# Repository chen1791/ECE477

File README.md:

# ECE477
Files for ECE 477 Smart Cart senior design project for Team 4.

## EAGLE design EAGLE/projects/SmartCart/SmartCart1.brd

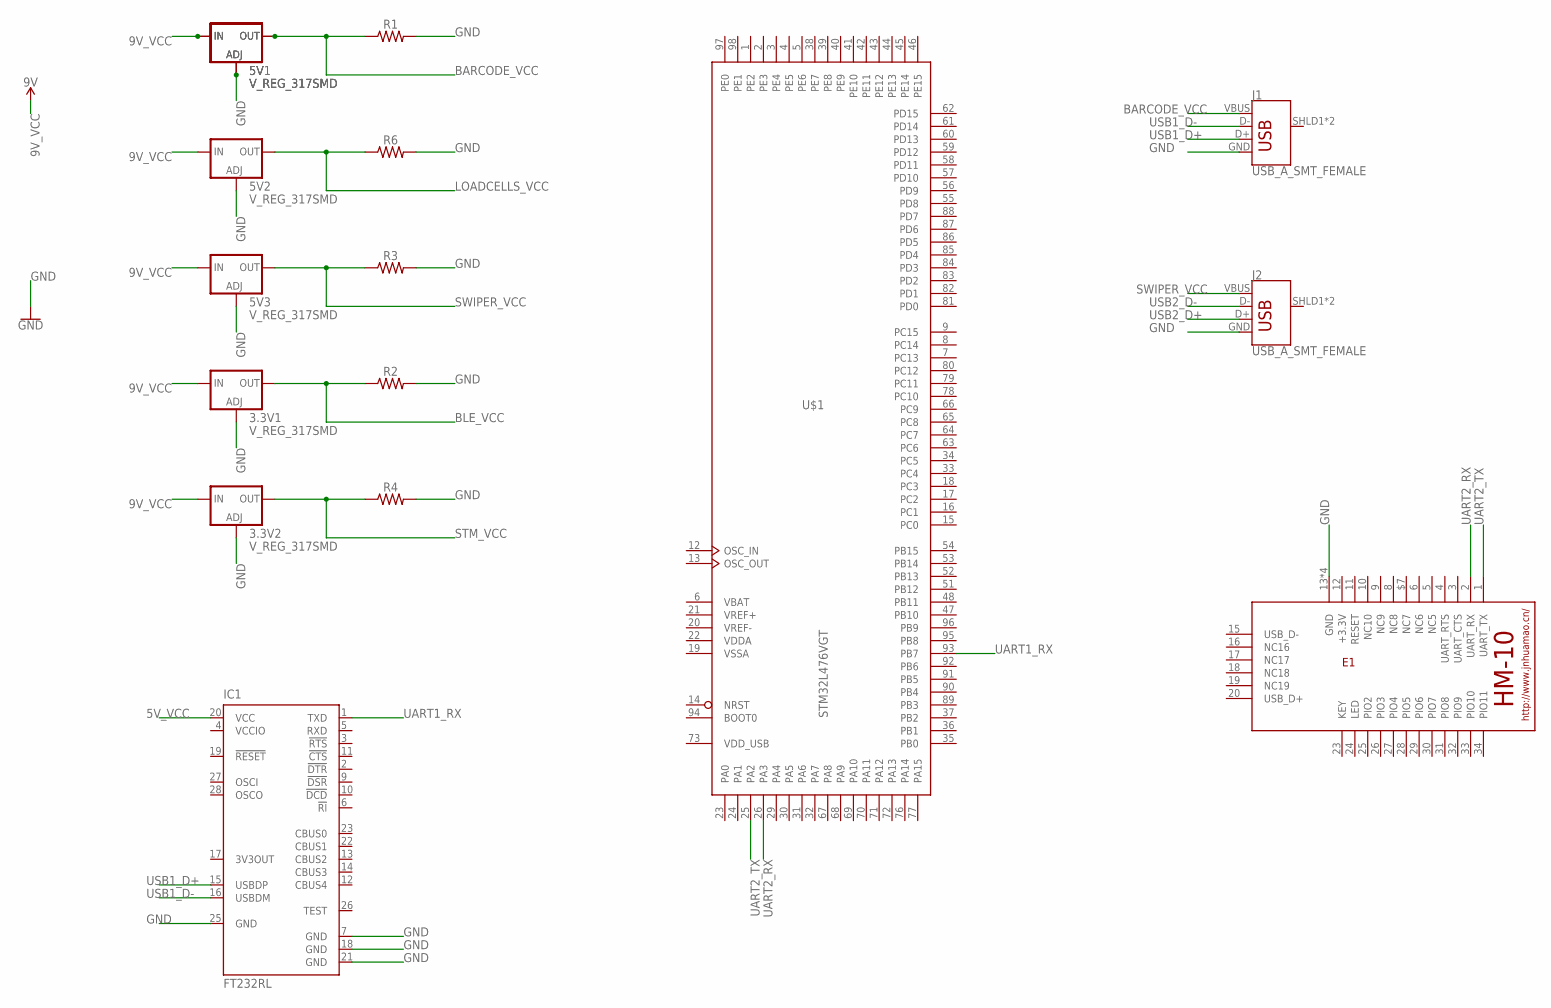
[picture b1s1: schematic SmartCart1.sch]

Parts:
3.3V1, 3.3V2, 5V, 5V1, 5V2, 5V3: V_REG_317SMD; SOT223
E1: HM-10-BOARD; 26.9X13X2.2_BOARD
IC1: FT232RL; SSOP28
J1, J2: USB_A_SMT_FEMALE; USB-A-S-SILK-FEMALE
R1, R2, R3, R4, R6: 0805
U$1: STM32L476VGT; LQFP100

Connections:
5V_VCC: IC1.20 (VCC)
9V_VCC: 3.3V1.3 (IN), 3.3V2.3 (IN), 5V.3 (IN), 5V1.3 (IN), 5V2.3 (IN), 5V3.3 (IN)
BARCODE_VCC: 5V.2 (OUT), 5V1.2 (OUT), J1.VBUS, R1.1
BLE_VCC: 3.3V1.2 (OUT), R2.1
GND: 3.3V1.1 (ADJ), 3.3V2.1 (ADJ), 5V.1 (ADJ), 5V1.1 (ADJ), 5V2.1 (ADJ), 5V3.1 (ADJ), E1.6 (NC6), E1.13 (GND), E1.14 (GND), E1.21 (GND), E1.22 (GND), IC1.7 (GND), IC1.18 (GND), IC1.21 (GND), IC1.25 (GND), J1.GND, J2.GND, R1.2, R2.2, R3.2, R4.2, R6.2
LOADCELLS_VCC: 5V2.2 (OUT), R6.1
STM_VCC: 3.3V2.2 (OUT), R4.1
SWIPER_VCC: 5V3.2 (OUT), E1.9 (NC9), J2.VBUS, R3.1
UART1_RX: IC1.1 (TXD), U$1.93 (PB7)
UART2_RX: E1.2 (UART_RX), U$1.26 (PA3)
UART2_TX: E1.1 (UART_TX), U$1.25 (PA2)
USB1_D+: IC1.15 (USBDP), J1.D+
USB1_D-: IC1.16 (USBDM), J1.D-
USB2_D+: E1.$7 (NC7), J2.D+
USB2_D-: E1.8 (NC8), J2.D-
VBAT: U$1.6 (VBAT)
VCCIO: IC1.4 (VCCIO)
VDD: U$1.11 (VDD), U$1.28 (VDD), U$1.50 (VDD), U$1.75 (VDD), U$1.100 (VDD)
VDDA: U$1.22 (VDDA)
VDD_USB: U$1.73 (VDD_USB)
VREF+: U$1.21 (VREF+)
VREF-: U$1.20 (VREF-)
VSS: U$1.10 (VSS), U$1.27 (VSS), U$1.49 (VSS), U$1.74 (VSS), U$1.99 (VSS)
VSSA: U$1.19 (VSSA)

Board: 2 copper layers, 16 parts (0 on the bottom side), 16 nets, no tracks yet.

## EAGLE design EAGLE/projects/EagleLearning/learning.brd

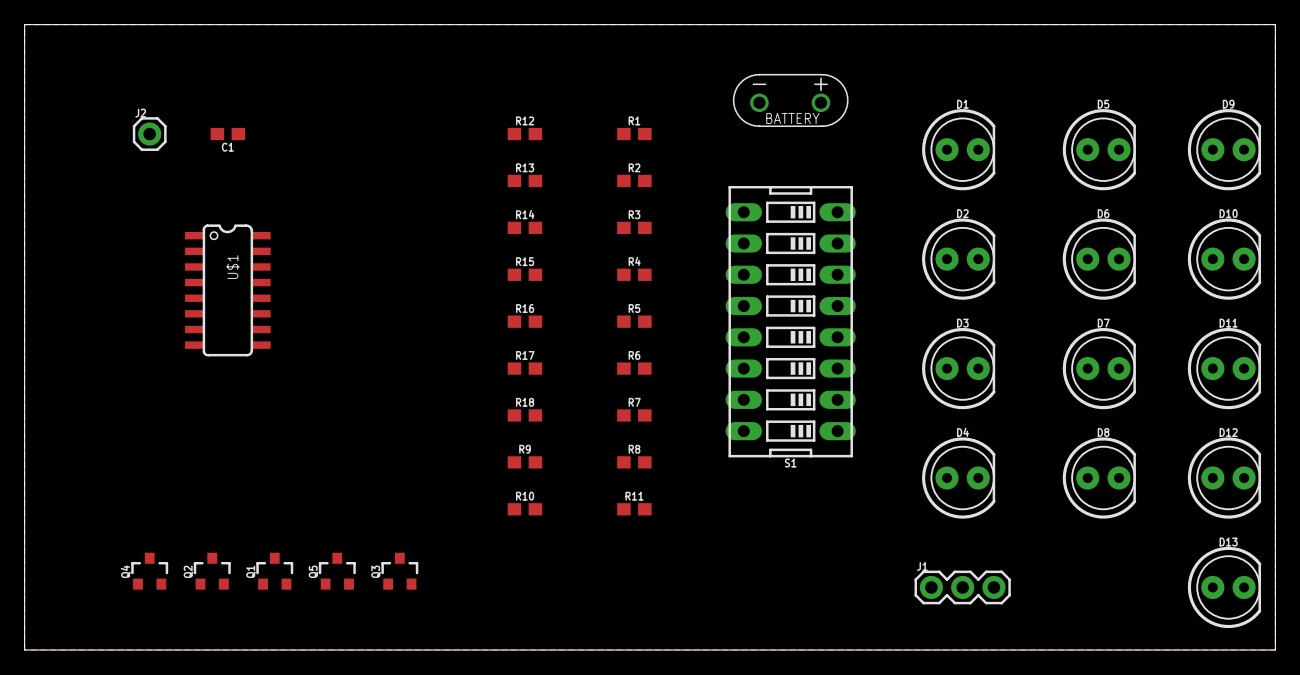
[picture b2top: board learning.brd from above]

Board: 2 copper layers, 101.6 x 50.8 mm, 42 parts (0 on the bottom side), 31 nets, no tracks yet.

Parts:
C1: 0.1uF; 0603
D1, D2, D3, D4, D5, D6, D7, D8, D9, D10, D11, D12, D13: LED_5MM
J1: 1X03
J2: 1X01
Q1, Q2, Q3, Q4, Q5: SOT23-3
R1, R2, R3, R4, R5, R6, R7, R8, R18: 10k; 0603
R9, R10, R11, R12, R13, R14, R15, R16, R17: 51; 0603
S1: DIPSWITCH-08
U$1: CD74HC283; SO016
U$2: AAA_BATTERIES; WIRE_LEADS

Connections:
3.3V: C1.1, D9.A, D10.A, D11.A, D12.A, D13.A, J2.1, U$1.16
A0: D5.A, R4.1, R9.1, S1.4
A1: D6.A, R3.1, R11.1, S1.3
A2: D7.A, R2.1, R13.1, S1.2
A3: D8.A, R1.1, R15.1, S1.1
B0: D1.A, R8.1, R10.1, S1.8
B1: D2.A, R7.1, R12.1, S1.7
B2: D3.A, R6.1, R14.1, S1.6
B3: D4.A, R5.1, R16.1, S1.5
CIN: J1.1, R17.1
COUT: J1.3, Q5.1, U$1.9
GND: C1.2, D1.K, D2.K, D3.K, D4.K, D5.K, D6.K, D7.K, D8.K, J1.2, Q1.2, Q2.2, Q3.2, Q4.2, Q5.2, R1.2, R2.2, R3.2, R4.2, R5.2, R6.2, R7.2, R8.2, R18.1, U$1.8, U$2.P$1
unnamed: R10.2, U$1.6
unnamed: R12.2, U$1.2
unnamed: R13.2, U$1.14
unnamed: R15.2, U$1.12
unnamed: R17.2, R18.2, U$1.7
unnamed: R14.2, U$1.15
unnamed: R9.2, U$1.5
unnamed: R16.2, U$1.11
unnamed: R11.2, U$1.3
unnamed: D9.K, Q1.3
unnamed: D10.K, Q2.3
unnamed: D11.K, Q3.3
unnamed: D12.K, Q4.3
unnamed: D13.K, Q5.3
unnamed: Q1.1, U$1.4
unnamed: Q2.1, U$1.1
unnamed: Q3.1, U$1.13
unnamed: Q4.1, U$1.10
VCC: S1.9, S1.10, S1.11, S1.12, S1.13, S1.14, S1.15, S1.16, U$2.P$2

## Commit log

2019-02-13 Added initial Eagle files
2019-02-13 Deleted the EAGLE files Tiffany originally included
2019-02-14 Added EAGLE folder with initial schematic
2019-02-24 2/23/2019

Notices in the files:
parts and their libraries:
SparkFun-Capacitors: Licensing: Creative Commons ShareAlike 4.0 International - https://creativecommons.org/licenses/by-sa/4.0
